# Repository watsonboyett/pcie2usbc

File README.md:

# miniPCIe to USB-C Adaptoid

A PCIe to USB-C adapter board -- plugs into a PCIe 1x card slot to breakout the data and clock lanes to a USB-C connector. 
Includes AC coupling caps and jumper resistors to aid in debugging/hacking.
Tested up to PCIe Gen 2 at 5.0 Gbps (though threre's plenty of room for improving the signal integrity).

[*] in 2nd step updating to PCIe 3.0 Standart

### Schematic

#### 
#### 
#### 

### PCB Bottom Side

#### 

### PCB Top Side

####

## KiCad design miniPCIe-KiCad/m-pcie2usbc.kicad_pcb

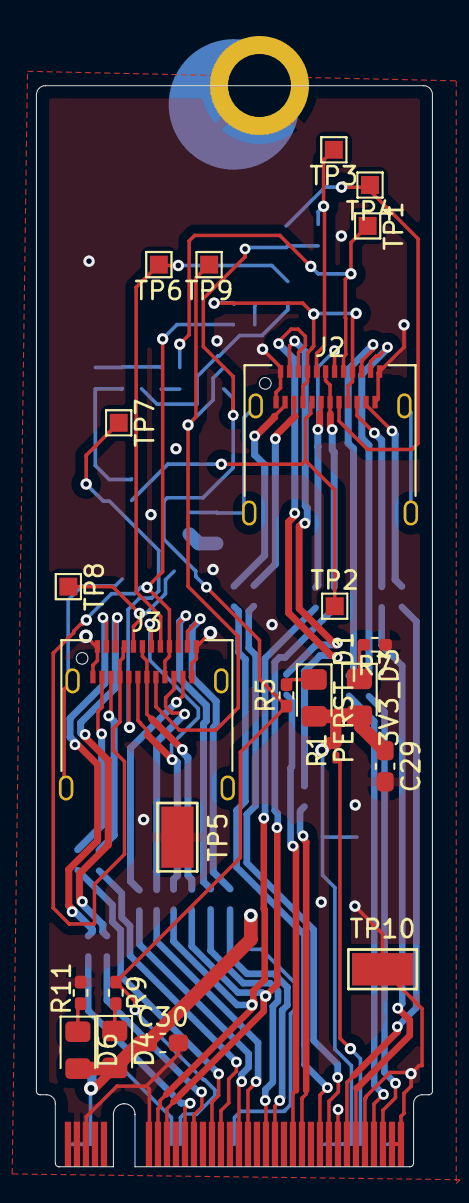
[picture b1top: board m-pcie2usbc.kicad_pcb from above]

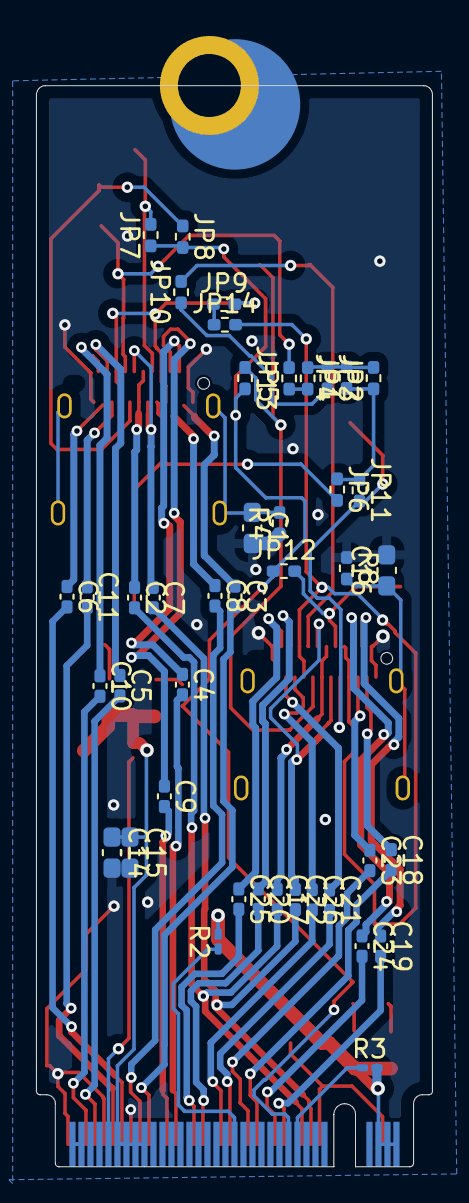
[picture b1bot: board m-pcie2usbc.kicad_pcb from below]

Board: 4 copper layers, 22.0 x 60.1 mm, 66 parts (42 on the bottom side), 65 nets.

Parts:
3V3_D3: LED; LED_0805_2012Metric_Pad1.15x1.40mm_HandSolder
C1, C15, C16, C30: 100n; C_0603_1608Metric_Pad1.08x0.95mm_HandSolder
C2, C3, C4, C5, C6, C7, C8, C9, C10, C11, C17, C18, C19, C20, C21, C22, C23, C24, C25, C26: 100n; C_0402_1005Metric_Pad0.74x0.62mm_HandSolder
C14, C29: 1u; C_0603_1608Metric_Pad1.08x0.95mm_HandSolder
D4, D6: LED; LED_0805_2012Metric_Pad1.15x1.40mm_HandSolder
J1: M.2-M-KEY
J2, J3: USB_C_Receptacle; USB_C_Receptacle_Amphenol_12401610E4-2A
JP1, JP2, JP3, JP4, JP5, JP6, JP7, JP8, JP9, JP10, JP11, JP12, JP13, JP14: 0; R_0402_1005Metric_Pad0.72x0.64mm_HandSolder
PERST_D1: LED; LED_0805_2012Metric_Pad1.15x1.40mm_HandSolder
R1, R2, R3: 10k; R_0201_0603Metric_Pad0.64x0.40mm_HandSolder
R4, R8: 100k; R_0402_1005Metric_Pad0.72x0.64mm_HandSolder
R5, R7, R9, R11: 2.2k; R_0402_1005Metric_Pad0.72x0.64mm_HandSolder
TP1, TP2, TP3, TP4, TP6, TP7, TP8, TP9: TestPoint; TestPoint_Pad_1.0x1.0mm
TP5, TP10: TestPoint; TestPoint_Keystone_5015_Micro-Minature

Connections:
+3V3: 3V3_D3.2 (A), C14.1, C15.1, C29.1, C30.1, D4.2 (A), D6.2 (A), J1.2 (3V3), J1.4 (3V3), J1.12 (3V3), J1.14 (3V3), J1.16 (3V3), J1.18 (3V3), J1.70 (3V3), J1.72 (3V3), J1.74 (3V3), PERST_D1.2 (A), R1.2, R2.2, R3.2
/CLKREQ_N: J1.52 (~CLKREQ/NC), R3.1
/PER0_N: C23.2, J1.41 (PER0-/SATA_B+)
/PER0_P: C18.2, J1.43 (PER0+/SATA_B-)
/PER1_N: C25.2, J1.29 (PER1-)
/PER1_P: C20.2, J1.31 (PER1+)
/PER2_N: C8.2, J1.17 (PER2-)
/PER2_P: C3.2, J1.19 (PER2+)
/PER3_N: C10.2, J1.5 (PER3-)
/PER3_P: C5.2, J1.7 (PER3+)
/PERST_N: J1.50 (~PERST/NC), JP7.1, JP8.2, JP12.1, JP13.2, R5.1, R9.1
/PET0_N: C24.2, J1.47 (PET0-/SATA_A-)
/PET0_P: C19.2, J1.49 (PET0+/SATA_A+)
/PET1_N: C26.2, J1.35 (PET1-)
/PET1_P: C21.2, J1.37 (PET1+)
/PET2_N: C9.2, J1.23 (PET2-)
/PET2_P: C4.2, J1.25 (PET2+)
/PET3_N: C11.2, J1.11 (PET3-)
/PET3_P: C6.2, J1.13 (PET3+)
/PRSNT1: JP2.1, JP4.1, JP6.1, JP11.1
/PRSNT_SEL: JP1.1, JP2.2, JP3.1, JP4.2
/REFCLK_N: C2.2, C17.2, J1.53 (REFCLK-)
/REFCLK_P: C7.2, C22.2, J1.55 (REFCLK+)
/USB-C-Lane1-2/CC1: J2.A5 (CC1), JP7.2, TP3.1
/USB-C-Lane1-2/CC2: J2.B5 (CC2), JP8.1, TP4.1
/USB-C-Lane1-2/D_N: C7.1, J2.A7 (D-), J2.B7 (D-)
/USB-C-Lane1-2/D_P: C2.1, J2.A6 (D+), J2.B6 (D+)
/USB-C-Lane1-2/PRSNT2_N: JP1.2, JP5.1
/USB-C-Lane1-2/RX1_N: C8.1, J2.B10 (RX1-)
/USB-C-Lane1-2/RX1_P: C3.1, J2.B11 (RX1+)
/USB-C-Lane1-2/RX2_N: C10.1, J2.A11 (RX2+)
/USB-C-Lane1-2/RX2_P: C5.1, J2.A10 (RX2-)
/USB-C-Lane1-2/SBU1: J2.A8 (SBU1), JP5.2, TP1.1
/USB-C-Lane1-2/SBU2: J2.B8 (SBU2), JP6.2, TP2.1
/USB-C-Lane1-2/TX1_N: C9.1, J2.A3 (TX1-)
/USB-C-Lane1-2/TX1_P: C4.1, J2.A2 (TX1+)
/USB-C-Lane1-2/TX2_N: C11.1, J2.B3 (TX2-)
/USB-C-Lane1-2/TX2_P: C6.1, J2.B2 (TX2+)
/USB-C-Lane1-2/VBUS: J2.A4 (VBUS), J2.A9 (VBUS), J2.B4 (VBUS), J2.B9 (VBUS), JP9.2
/USB-C-Lane1-3/CC1: J3.A5 (CC1), JP12.2, TP8.1
/USB-C-Lane1-3/CC2: J3.B5 (CC2), JP13.1, TP9.1
/USB-C-Lane1-3/D_N: C22.1, J3.A7 (D-), J3.B7 (D-)
/USB-C-Lane1-3/D_P: C17.1, J3.A6 (D+), J3.B6 (D+)
/USB-C-Lane1-3/PRSNT2_N: JP3.2, JP10.1
/USB-C-Lane1-3/RX1_N: C23.1, J3.B10 (RX1-)
/USB-C-Lane1-3/RX1_P: C18.1, J3.B11 (RX1+)
/USB-C-Lane1-3/RX2_N: C25.1, J3.A11 (RX2+)
/USB-C-Lane1-3/RX2_P: C20.1, J3.A10 (RX2-)
/USB-C-Lane1-3/SBU1: J3.A8 (SBU1), JP10.2, TP6.1
/USB-C-Lane1-3/SBU2: J3.B8 (SBU2), JP11.2, TP7.1
/USB-C-Lane1-3/TX1_N: C24.1, J3.A3 (TX1-)
/USB-C-Lane1-3/TX1_P: C19.1, J3.A2 (TX1+)
/USB-C-Lane1-3/TX2_N: C26.1, J3.B3 (TX2-)
/USB-C-Lane1-3/TX2_P: C21.1, J3.B2 (TX2+)
/USB-C-Lane1-3/VBUS: J3.A4 (VBUS), J3.A9 (VBUS), J3.B4 (VBUS), J3.B9 (VBUS), JP14.2
/VBUS_H: JP9.1, JP14.1
GND: C1.2, C14.2, C15.2, C16.2, C29.2, C30.2, J1.1 (GND), J1.3 (GND), J1.9 (GND), J1.15 (GND), J1.21 (GND), J1.27 (GND), J1.33 (GND), J1.39 (GND), J1.45 (GND), J1.51 (GND), J1.57 (GND), J1.71 (GND), J1.73 (GND), J1.75 (GND), J1.MOUNTING-HOLE (GND), J2.A1 (GND), J2.A12 (GND), J2.B1 (GND), J2.B12 (GND), J3.A1 (GND), J3.A12 (GND), J3.B1 (GND), J3.B12 (GND), R4.1, R7.1, R8.1, R11.1, TP5.1, TP10.1
unnamed: 3V3_D3.1 (K), R7.2
unnamed: D4.1 (K), R9.2
unnamed: D6.1 (K), R11.2
unnamed: J1.10 (DAS/~DSS), R1.1
unnamed: J1.38 (DEVSLP), R2.1
unnamed: C1.1, J2.S1 (SHIELD), R4.2
unnamed: C16.1, J3.S1 (SHIELD), R8.2
unnamed: PERST_D1.1 (K), R5.2

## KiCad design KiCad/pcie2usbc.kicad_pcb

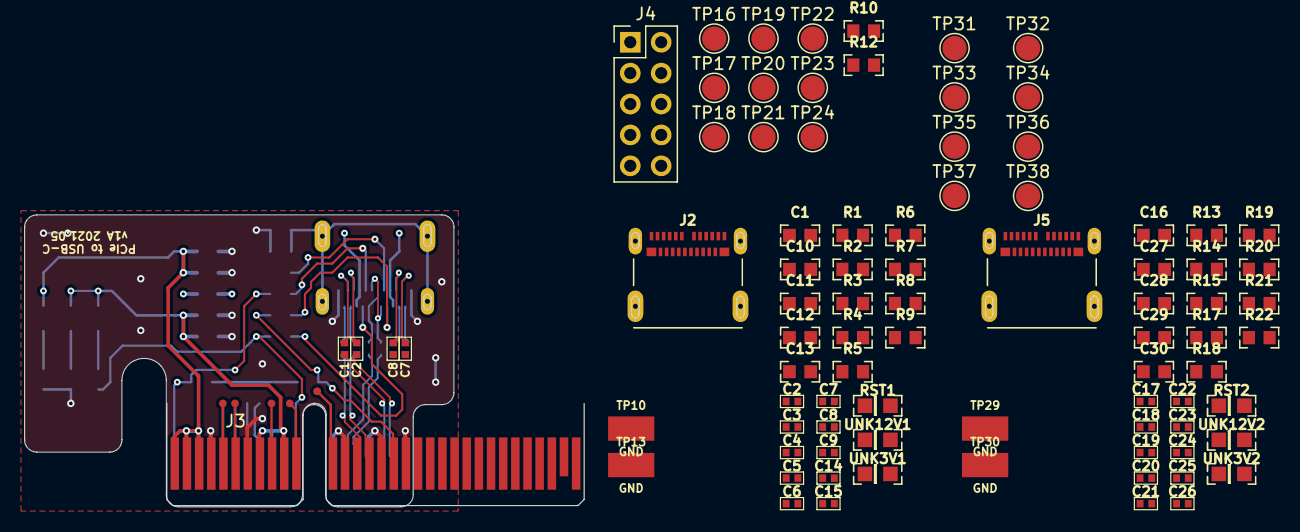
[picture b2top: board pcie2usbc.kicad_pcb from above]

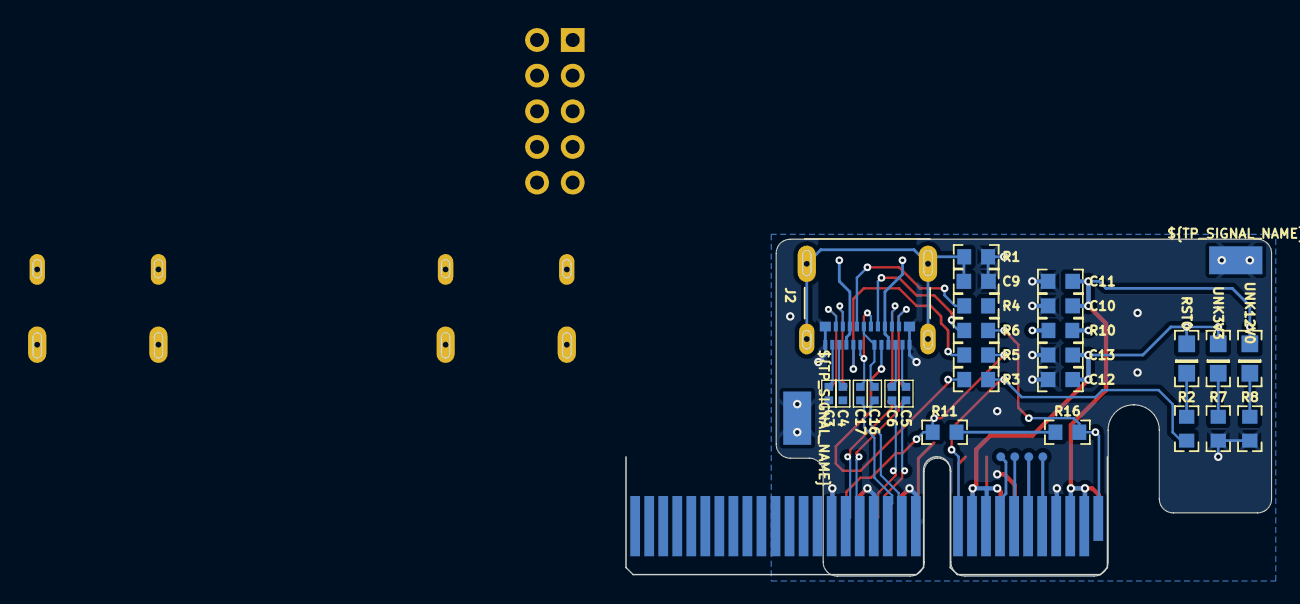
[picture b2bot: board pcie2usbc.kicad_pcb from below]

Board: 4 copper layers, 126 parts (32 on the bottom side), 100 nets.

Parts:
C1, C2, C2#2, C3, C3#2, C4, C4#2, C5, C5#2, C6, C6#2, C7, C7#2, C8, C8#2, C9, C14, C15, C16#2, C17, C17#2, C18, C19, C20, C21, C22, C23, C24, C25, C26: 100n; C0402
C1#2, C9#2, C11, C11#2, C13, C13#2, C16, C28, C30: 100n; C0603K
C10, C10#2, C12, C12#2, C27, C29: 1u; C0603K
J2, J2#2, J5: USB-C-MLX; MOLEX_105450-0101
J3: Bus_PCI_Express_x4; BUS_PCIexpress_x4
J4: Conn_02x05_Top_Bottom; PinHeader_2x05_P2.54mm_Vertical
R1, R3, R3#2, R4, R4#2, R5, R5#2, R6, R6#2, R10, R10#2, R11, R12, R16, R17, R18, R19, R20, R21: 0; R0603
R1#2, R9, R22: 100k; R0603
R2, R2#2, R7#2, R8, R13, R15: 2.2k; R0603
R7, R8#2, R14: 10k; R0603
RST0: SML0805
RST1, RST2: LEDSML0805; SML0805
TP1, TP2, TP3, TP4, TP5, TP6, TP7, TP8, TP9, TP11, TP12, TP16, TP21#2: TPB0,635; B0,635
TP10, TP10#2, TP13, TP13#2, TP29, TP30: TPTP38X20; TP38X20
TP16#2, TP17, TP18, TP19, TP20, TP21, TP22, TP23, TP24, TP31, TP32, TP33, TP34, TP35, TP36, TP37, TP38: TestPoint; TestPoint_Pad_D2.0mm
UNK3V1, UNK3V2, UNK12V1, UNK12V2: LEDSML0805; SML0805
UNK3V3, UNK12V0: SML0805

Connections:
3V3: C12#2.1, C13#2.1, RST0.A, UNK3V3.A
12V0: C10#2.1, C11#2.1, UNK12V0.A
+3V3: C12.1, C13.1, C29.1, C30.1, J3.A9 (+3.3V), J3.A10 (+3.3V), J3.B8 (+3.3V), J3.B10 (3.3Vaux), RST1.A, RST2.A, UNK3V1.A, UNK3V2.A
+12V: C10.1, C11.1, C27.1, C28.1, J3.A2 (+12V), J3.A3 (+12V), J3.B1 (+12V), J3.B2 (+12V), J3.B3 (+12V), UNK12V1.A, UNK12V2.A
/CLKREQ_N: J3.B12 (RSVD), J4.5, TP20.1
/PER0_N: C7.2, J3.A17 (PERn0)
/PER0_P: C2.2, J3.A16 (PERp0)
/PER1_N: C8.2, J3.A22 (PERn1)
/PER1_P: C3.2, J3.A21 (PERp1)
/PER2_N: C23.2, J3.A26 (PERn2)
/PER2_P: C18.2, J3.A25 (PERp2)
/PER3_N: C22.2, J3.A30 (PERn3)
/PER3_P: C17.2, J3.A29 (PERp3)
/PERST_N: J3.A11 (~PERST), R2.1, R5.1, R6.2, R13.1, R20.1, R21.2
/PET0_N: C9.2, J3.B15 (PETn0)
/PET0_P: C4.2, J3.B14 (PETp0)
/PET1_N: C14.2, J3.B20 (PETn1)
/PET1_P: C5.2, J3.B19 (PETp1)
/PET2_N: C25.2, J3.B24 (PETn2)
/PET2_P: C20.2, J3.B23 (PETp2)
/PET3_N: C24.2, J3.B28 (PETn3)
/PET3_P: C19.2, J3.B27 (PETp3)
/PRSNT1: J3.A1 (~PRSNT1), R12.1
/PRSNT1_N: R4.1, R19.1
/PRSNT2: J3.B17 (~PRSNT2), J3.B31 (~PRSNT2), R10.2
/PRSNT2_N: R3.1, R18.1
/PRSNT_SEL: R10.1, R12.2
/REFCLK_N: C15.2, C26.2, J3.A14 (REFCLK-)
/REFCLK_P: C6.2, C21.2, J3.A13 (REFCLK+)
/SMCLK: J3.B5 (SMCLK), J4.1, TP16#2.1
/SMDAT: J3.B6 (SMDAT), J4.2, TP17.1
/TCK: J3.A5 (JTAG2), J4.6, TP21.1
/TDI: J3.A6 (JTAG3), J4.7, TP22.1
/TDO: J3.A7 (JTAG4), J4.8, TP23.1
/TMS: J3.A8 (JTAG5), J4.9, TP24.1
/TRST_N: J3.B9 (JTAG1), J4.3, TP18.1
/USB-C Lane1+2/CC1: J2.A5 (CC1), R5.2, TP35.1
/USB-C Lane1+2/CC2: J2.B5 (CC2), R6.1, TP37.1
/USB-C Lane1+2/D_N: C15.1, J2.A7 (DA-), J2.B7 (DB-)
/USB-C Lane1+2/D_P: C6.1, J2.A6 (DA+), J2.B6 (DB+)
/USB-C Lane1+2/RX1_N: C7.1, J2.B10 (RX1-)
/USB-C Lane1+2/RX1_P: C2.1, J2.B11 (RX1+)
/USB-C Lane1+2/RX2_N: C8.1, J2.A10 (RX2-)
/USB-C Lane1+2/RX2_P: C3.1, J2.A11 (RX2+)
/USB-C Lane1+2/SBU1: J2.A8 (SBU1), R3.2, TP31.1
/USB-C Lane1+2/SBU2: J2.B8 (SBU2), R4.2, TP33.1
/USB-C Lane1+2/TX1_N: C9.1, J2.A3 (TX1-)
/USB-C Lane1+2/TX1_P: C4.1, J2.A2 (TX1+)
/USB-C Lane1+2/TX2_N: C14.1, J2.B3 (TX2-)
/USB-C Lane1+2/TX2_P: C5.1, J2.B2 (TX2+)
/USB-C Lane1+2/VBUS: J2.A4 (VBUS), J2.A9 (VBUS), J2.B4 (VBUS), J2.B9 (VBUS), R1.2
/USB-C Lane3+4/CC1: J5.A5 (CC1), R20.2, TP36.1
/USB-C Lane3+4/CC2: J5.B5 (CC2), R21.1, TP38.1
/USB-C Lane3+4/D_N: C26.1, J5.A7 (DA-), J5.B7 (DB-)
/USB-C Lane3+4/D_P: C21.1, J5.A6 (DA+), J5.B6 (DB+)
/USB-C Lane3+4/RX1_N: C22.1, J5.B10 (RX1-)
/USB-C Lane3+4/RX1_P: C17.1, J5.B11 (RX1+)
/USB-C Lane3+4/RX2_N: C23.1, J5.A10 (RX2-)
/USB-C Lane3+4/RX2_P: C18.1, J5.A11 (RX2+)
/USB-C Lane3+4/SBU1: J5.A8 (SBU1), R18.2, TP32.1
/USB-C Lane3+4/SBU2: J5.B8 (SBU2), R19.2, TP34.1
/USB-C Lane3+4/TX1_N: C24.1, J5.A3 (TX1-)
/USB-C Lane3+4/TX1_P: C19.1, J5.A2 (TX1+)
/USB-C Lane3+4/TX2_N: C25.1, J5.B3 (TX2-)
/USB-C Lane3+4/TX2_P: C20.1, J5.B2 (TX2+)
/USB-C Lane3+4/VBUS: J5.A4 (VBUS), J5.A9 (VBUS), J5.B4 (VBUS), J5.B9 (VBUS), R17.2
/VBUS_H: J4.10, R1.1, R17.1
/WAKE_N: J3.B11 (~WAKE), J4.4, TP19.1
CC1: J2#2.A5, R3#2.2, TP21#2.TP
CC2: J2#2.B5, R4#2.1, TP16.TP
D_N: C17#2.1, J2#2.A7, J2#2.B7
D_P: C16#2.1, J2#2.A6, J2#2.B6
GND: C1#2.2, C9#2.2, C10.2, C10#2.2, C11.2, C11#2.2, C12.2, C12#2.2, C13.2, C13#2.2, C16.2, C27.2, C28.2, C29.2, C30.2, J2.A1 (GND), J2.A12 (GND), J2.B1 (GND), J2.B12 (GND), J2#2.A1, J2#2.A12, J2#2.B1, J2#2.B12, J3.A4 (GND), J3.A12 (GND), J3.A15 (GND), J3.A18 (GND), J3.A20 (GND), J3.A23 (GND), J3.A24 (GND), J3.A27 (GND), J3.A28 (GND), J3.A31 (GND), J3.B4 (GND), J3.B7 (GND), J3.B13 (GND), J3.B16 (GND), J3.B18 (GND), J3.B21 (GND), J3.B22 (GND), J3.B25 (GND), J3.B26 (GND), J3.B29 (GND), J3.B32 (GND), J5.A1 (GND), J5.A12 (GND), J5.B1 (GND), J5.B12 (GND), R1#2.1, R7.1, R7#2.1, R8.1, R8#2.1, R9.1, R14.1, R15.1, R22.1, TP10.TP, TP10#2.TP, TP13.TP, TP13#2.TP, TP29.TP, TP30.TP
unnamed: R8#2.2, UNK12V0.C
unnamed: R7#2.2, UNK3V3.C
unnamed: R2#2.2, RST0.C
unnamed: C1#2.1, J2.S1 (SHIELD), J2.S2 (SHIELD), J2.S3 (SHIELD), J2.S4 (SHIELD), R9.2
unnamed: C16.1, J5.S1 (SHIELD), J5.S2 (SHIELD), J5.S3 (SHIELD), J5.S4 (SHIELD), R22.2
unnamed: R2.2, RST1.C
unnamed: R7.2, UNK12V1.C
unnamed: R8.2, UNK3V1.C
unnamed: R13.2, RST2.C
unnamed: R14.2, UNK12V2.C
unnamed: R15.2, UNK3V2.C
PERST_N: R2#2.1, R3#2.1
PRSNT1_N: R6#2.1, R16.1
PRSNT2_N: R5#2.1, R11.2
PRSNT_SEL: R11.1, R16.2
RX1_N: C2#2.1, J2#2.B10
RX1_P: C1.1, J2#2.B11
RX2_N: C4#2.1, J2#2.A10
RX2_P: C3#2.1, J2#2.A11
SBU1: J2#2.A8, R5#2.2, TP11.TP
SBU2: J2#2.B8, R6#2.2, TP12.TP
TX1_N: C6#2.1, J2#2.A3
TX1_P: C5#2.1, J2#2.A2
TX2_N: C8#2.1, J2#2.B3
TX2_P: C7#2.1, J2#2.B2
USB_SHLD1: C9#2.1, J2#2.S1, J2#2.S2, J2#2.S3, J2#2.S4, R1#2.2
VBUS: J2#2.A4, J2#2.A9, J2#2.B4, J2#2.B9, R10#2.2

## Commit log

2023-08-18 KiCad 4x version -- work in progress
2023-09-12 WIP - fine tune routing
    WIP - fine tune routing
2023-09-13 Layout completed
    Layout completed
2023-09-13 final Layout
    Layout done
2023-09-15 Layout completed / Readme updar
    finalized layout
    README.me updated
